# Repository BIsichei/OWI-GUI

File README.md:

# OWI-GUI
OWI robot arm GUI files

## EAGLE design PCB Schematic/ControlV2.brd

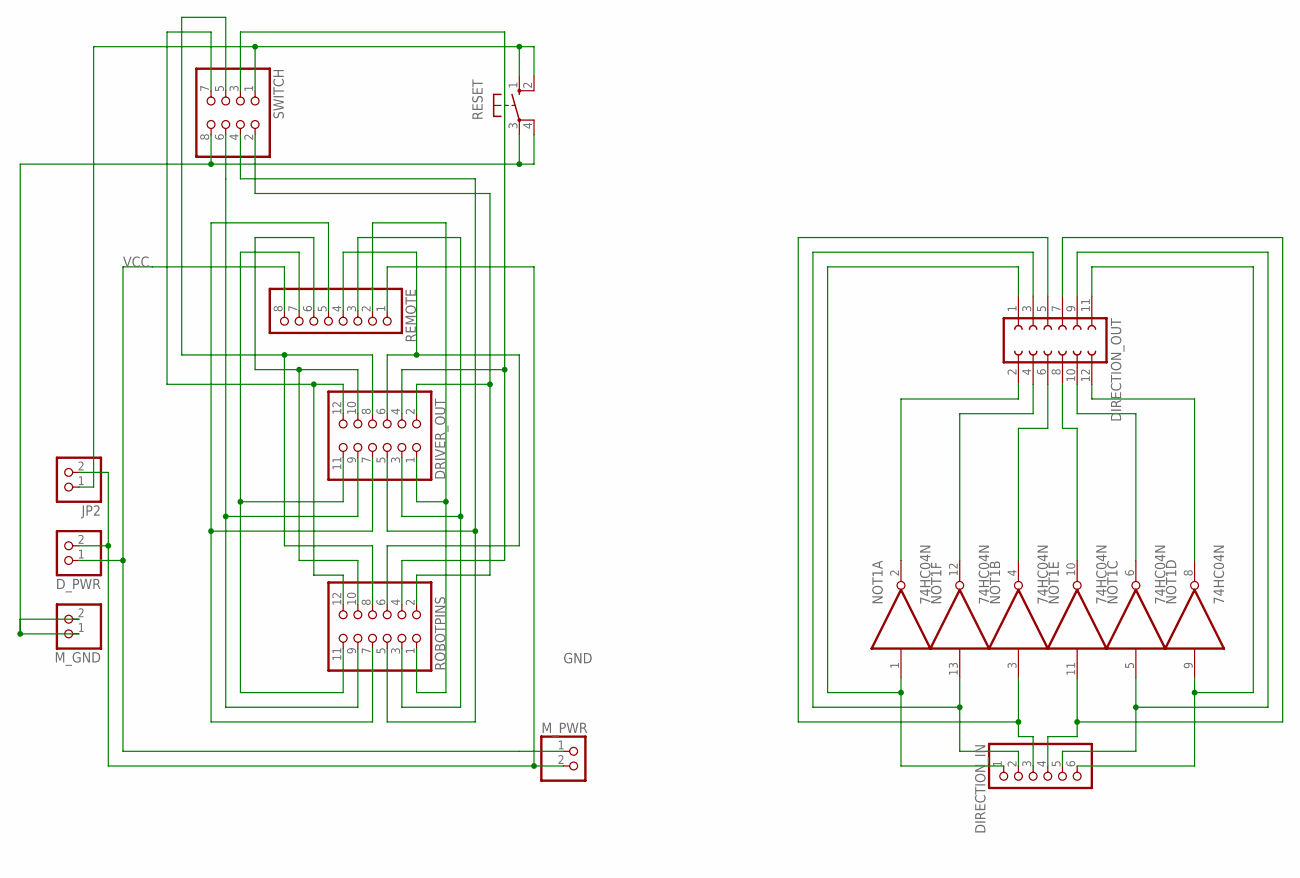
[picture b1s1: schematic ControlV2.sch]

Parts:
DIRECTION_IN: PINHD-1X6; 1X06
DIRECTION_OUT: FE06-2
DRIVER_OUT: PINHD-2X6; 2X06
D_PWR: PINHD-1X2; 1X02
JP2: PINHD-1X2; 1X02
M_GND: PINHD-1X2; 1X02
M_PWR: PINHD-1X2; 1X02
NOT1: 74HC04N; DIL14
REMOTE: PINHD-1X8; 1X08
RESET: 10-XX; B3F-10XX
ROBOTPINS: PINHD-2X6; 2X06
SWITCH: PINHD-2X4; 2X04

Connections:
GND: D_PWR.2, JP2.2, M_PWR.2, NOT1.7 (GND), REMOTE.1
unnamed: M_GND.1, M_GND.2, RESET.3, RESET.4 (P1), SWITCH.8
unnamed: JP2.1, RESET.1 (S), RESET.2 (S1), SWITCH.1
unnamed: DRIVER_OUT.2, ROBOTPINS.2, SWITCH.2
unnamed: DRIVER_OUT.4, ROBOTPINS.4, SWITCH.3
unnamed: DRIVER_OUT.6, REMOTE.4, ROBOTPINS.6
unnamed: DRIVER_OUT.12, ROBOTPINS.12, SWITCH.7
unnamed: DRIVER_OUT.10, REMOTE.6, ROBOTPINS.10
unnamed: DRIVER_OUT.8, ROBOTPINS.8, SWITCH.5
unnamed: DRIVER_OUT.11, REMOTE.7, ROBOTPINS.11
unnamed: DRIVER_OUT.9, ROBOTPINS.9, SWITCH.6
unnamed: DRIVER_OUT.7, REMOTE.5, ROBOTPINS.7
unnamed: DRIVER_OUT.5, ROBOTPINS.5, SWITCH.4
unnamed: DRIVER_OUT.3, REMOTE.3, ROBOTPINS.3
unnamed: DRIVER_OUT.1, REMOTE.2, ROBOTPINS.1
unnamed: DIRECTION_IN.1, DIRECTION_OUT.1, NOT1.1 (I)
unnamed: DIRECTION_IN.2, DIRECTION_OUT.3, NOT1.13 (I)
unnamed: DIRECTION_IN.3, DIRECTION_OUT.5, NOT1.3 (I)
unnamed: DIRECTION_IN.4, DIRECTION_OUT.7, NOT1.11 (I)
unnamed: DIRECTION_IN.5, DIRECTION_OUT.9, NOT1.5 (I)
unnamed: DIRECTION_IN.6, DIRECTION_OUT.11, NOT1.9 (I)
unnamed: DIRECTION_OUT.2, NOT1.2 (O)
unnamed: DIRECTION_OUT.12, NOT1.8 (O)
unnamed: DIRECTION_OUT.4, NOT1.12 (O)
unnamed: DIRECTION_OUT.6, NOT1.4 (O)
unnamed: DIRECTION_OUT.8, NOT1.10 (O)
unnamed: DIRECTION_OUT.10, NOT1.6 (O)
VCC: D_PWR.1, M_PWR.1, NOT1.14 (VCC), REMOTE.8

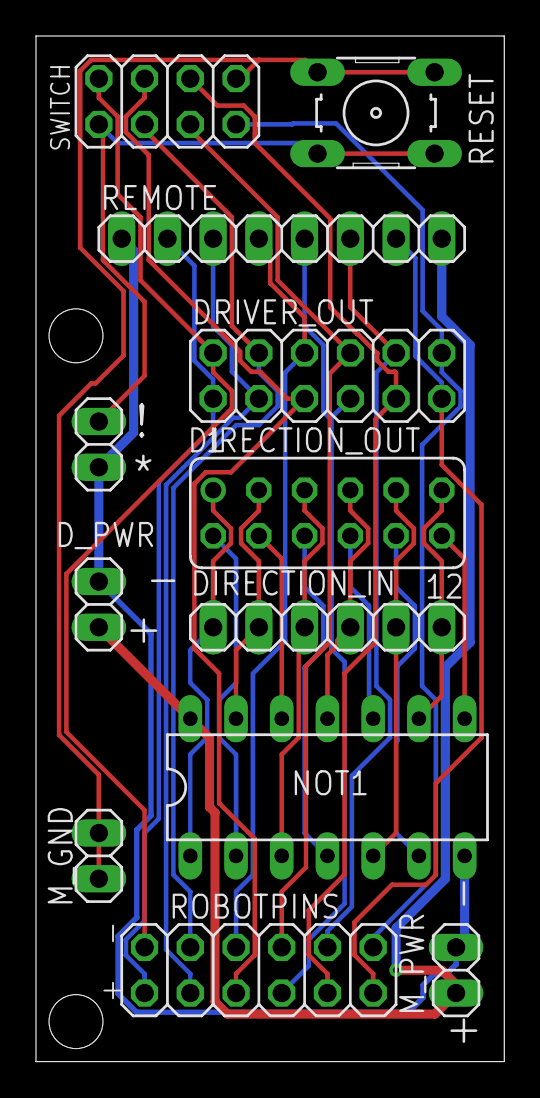
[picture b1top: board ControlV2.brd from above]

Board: 2 copper layers, 26.0 x 57.0 mm, 12 parts (0 on the bottom side), 28 nets.

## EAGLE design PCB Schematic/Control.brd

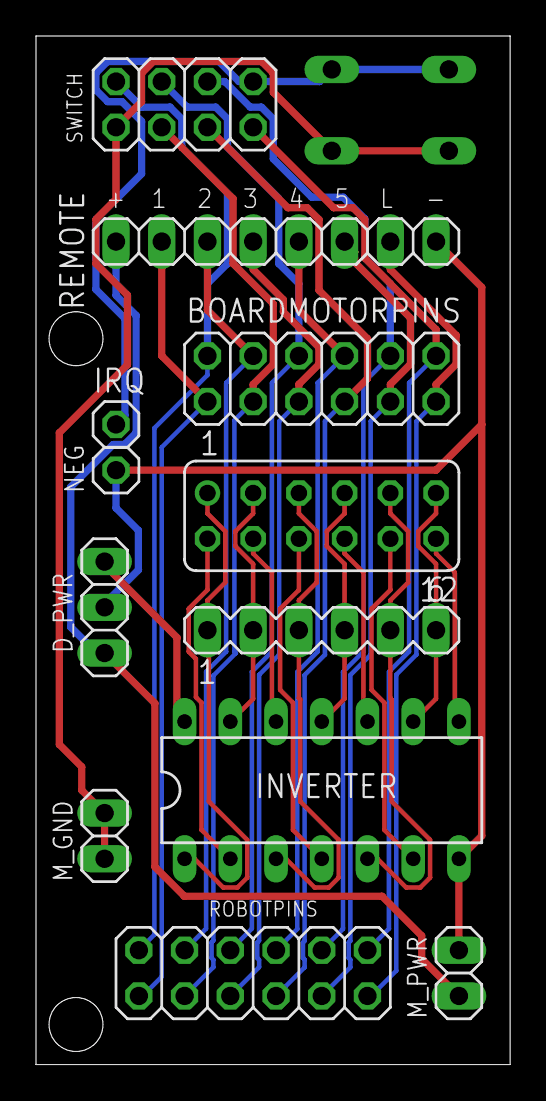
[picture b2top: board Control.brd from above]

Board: 2 copper layers, 26.3 x 57.1 mm, 13 parts (1 on the bottom side), 29 nets.

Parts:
BOARDMOTORPINS: 2X06
DIGITAL_IN: MA06-1
D_PWR: 1X03
INVERTER: 74LS04N; DIL14
IRQ: 1X01
M_GND: 1X02
M_PWR: 1X02
NEG: 1X01
REMOTE: 1X08
ROBOTPINS: 2X06
S1: B3F-10XX
SWITCH: 2X04
TOBOARD: FE06-2

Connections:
GND: D_PWR.2, INVERTER.7, M_PWR.2, NEG.1, REMOTE.8
unnamed: DIGITAL_IN.6, INVERTER.9, TOBOARD.11
unnamed: DIGITAL_IN.4, INVERTER.11, TOBOARD.7
unnamed: DIGITAL_IN.2, INVERTER.13, TOBOARD.3
unnamed: DIGITAL_IN.1, INVERTER.1, TOBOARD.1
unnamed: DIGITAL_IN.3, INVERTER.3, TOBOARD.5
unnamed: DIGITAL_IN.5, INVERTER.5, TOBOARD.9
unnamed: INVERTER.2, TOBOARD.2
unnamed: INVERTER.4, TOBOARD.6
unnamed: INVERTER.6, TOBOARD.10
unnamed: INVERTER.8, TOBOARD.12
unnamed: INVERTER.10, TOBOARD.8
unnamed: INVERTER.12, TOBOARD.4
unnamed: BOARDMOTORPINS.1, REMOTE.2, ROBOTPINS.1
unnamed: BOARDMOTORPINS.3, ROBOTPINS.3, SWITCH.3
unnamed: BOARDMOTORPINS.5, REMOTE.4, ROBOTPINS.5
unnamed: BOARDMOTORPINS.7, ROBOTPINS.7, SWITCH.5
unnamed: BOARDMOTORPINS.9, REMOTE.6, ROBOTPINS.9
unnamed: BOARDMOTORPINS.11, REMOTE.7, ROBOTPINS.11
unnamed: BOARDMOTORPINS.12, ROBOTPINS.12, SWITCH.7
unnamed: BOARDMOTORPINS.10, ROBOTPINS.10, SWITCH.6
unnamed: BOARDMOTORPINS.8, REMOTE.5, ROBOTPINS.8
unnamed: BOARDMOTORPINS.2, ROBOTPINS.2, SWITCH.2
unnamed: BOARDMOTORPINS.4, REMOTE.3, ROBOTPINS.4
unnamed: BOARDMOTORPINS.6, ROBOTPINS.6, SWITCH.4
unnamed: D_PWR.1, M_PWR.1, REMOTE.1
unnamed: M_GND.1, M_GND.2, S1.1, S1.2, SWITCH.1
unnamed: IRQ.1, S1.3, S1.4, SWITCH.8
VCC: D_PWR.3, INVERTER.14

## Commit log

2017-05-24 Stl file importers
    Files to read Binary STL data into the GUI function
2017-05-24 3d files
    Robot Model Files
2017-05-24 Create a
2017-05-24 M2 Gear
2017-05-24 M4 Tip
2017-05-24 General gear
2017-05-26 potholders/cut/groups
2017-06-06 Re-organizing
    grouping the model files together to reduce clutter
2017-06-06 Main Gui Function
2017-06-06 Arm 3d Models
    3d models for visualising the arm in the GUI
2017-06-06 Miscellaneous settings for the GUI
2017-06-06 Potentiometer Gears
    Dxf files for cutting out the Pot gears on Acrylic.
    To be cut on 6mm acrylic sheets
2017-06-06 Potentiometer Gears
    Dxf files for cutting out the Pot gears on Acrylic.
    To be cut on a 3-4mm thick acrylic sheet
2017-06-06 Potentiometer Gears
    Dxf files for cutting out the Pot gears on Acrylic.
    To be cut on a 2mm thick acrylic sheet
2017-06-06 Potentiometer Parts
    3d models for attaching the potentiometers to the robot arm
2017-06-06 Support Functions
2017-06-06 Arduino Functions
2017-06-06 Alternate control with Motor Drivers
    a variation of the main code to take advantage
    of PWM in controlling the arm's Joints
2017-06-16 Structure Change
    Changed the way the pin information
    is stored in the program to simplify
    some of the assignment functions.
2017-06-27 Removed Button Group function
    Removed the Buttongroup function and unneccesary 'eval' calls
    to improve code readability and practice good programming
    habits.
2017-07-07 Consistency Edits
2017-07-21 Increased Tolerance Value
    Increased tolerance Value,
    Edited the Pin save and Load callbacks to include the light pin
    Edited the getDir function to be more straightforward
    Fixed merge errors in the main Driver function and improperpin Function
    Updated teh NewDriverPins file to include the light pin
    Fixed the Analog Write function running with the wrong loop size
2017-08-04 Efficiency Update
    array searches are now independent on the size of the analog pins
2017-08-04 DH Table Update
    Added a DH table updater
2017-08-04 Most recent Lab arm Calibration
2017-08-04 Feedback Parts list
2017-08-04 New Pins settings
    Includes Light and IRQ pins
2017-08-04 Consistency Gear update
2017-08-10 Tests
2017-08-10 Test
2017-10-17 Compulsive Edits
2017-10-17 Archaic Function
2017-10-17 Cleanup
2018-07-26 Holder Cleanup
    Deleted redundant entries and ordered the gears by thickness
2018-07-27 Cleanup
    cleaned up Debug text
2018-08-01 Added Figure Binding
    Figures are now bound to a specific COM port. This means multiple bound windows can be open simultaneously.
    Arduinos can now be assigned to figures without relaunching.
    Clarified some variables.
2018-08-01 renamed main program
2018-08-01 Commentary
2018-08-01 updated function dependencies
2018-08-14 Commentary
    going through the code and cleaning up
2018-08-15 Schematic Update
    Updated Custom PCB Schematic
2018-09-10 UM2+ Gcode upload
    Gcode with settings for printing the 3d printed parts on an ultimaker 2+
2018-09-15 Holder Clarifications
    specified the thicknesses of the gears to be cut for attaching potentiomenters and implementing feedback.
